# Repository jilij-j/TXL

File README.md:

TXL is a project to build classical distortion FX as eurorack modules with CV.

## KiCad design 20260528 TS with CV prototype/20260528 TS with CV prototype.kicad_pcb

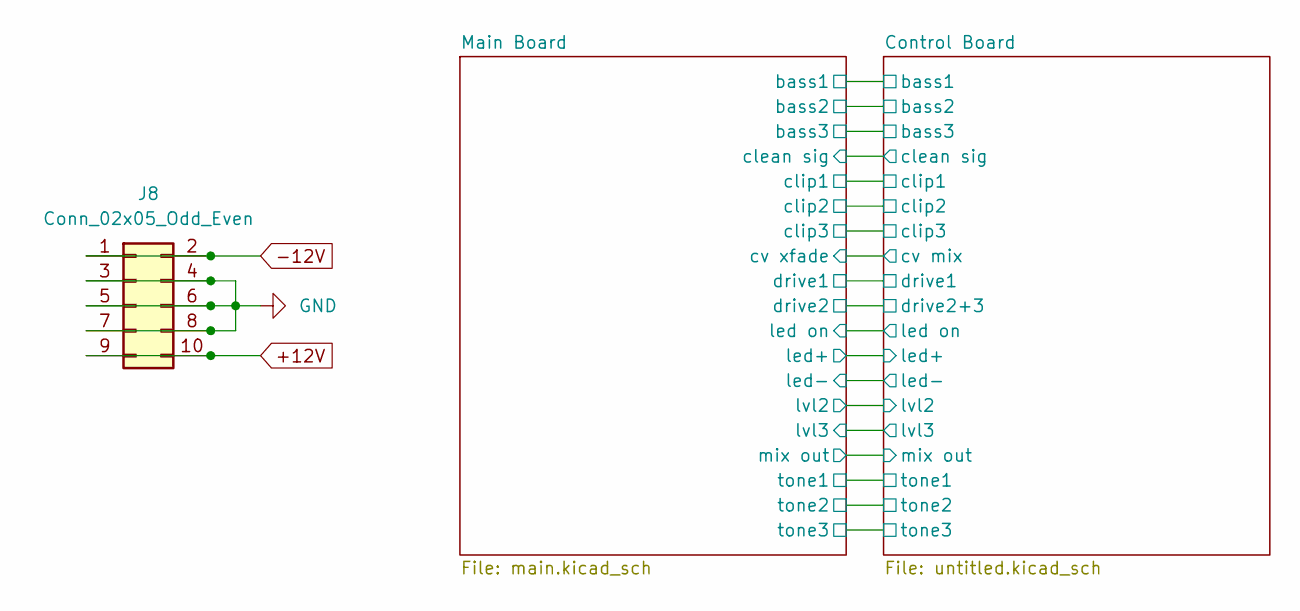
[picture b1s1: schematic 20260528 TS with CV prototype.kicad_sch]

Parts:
J8: Conn_02x05_Odd_Even; IDC-Header_2x05_P2.54mm_Vertical

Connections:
+12V: J8.9, J8.10; also elsewhere on the board
-12V: J8.1, J8.2; also elsewhere on the board
GND: J8.3, J8.4, J8.5, J8.6, J8.7, J8.8; also elsewhere on the board

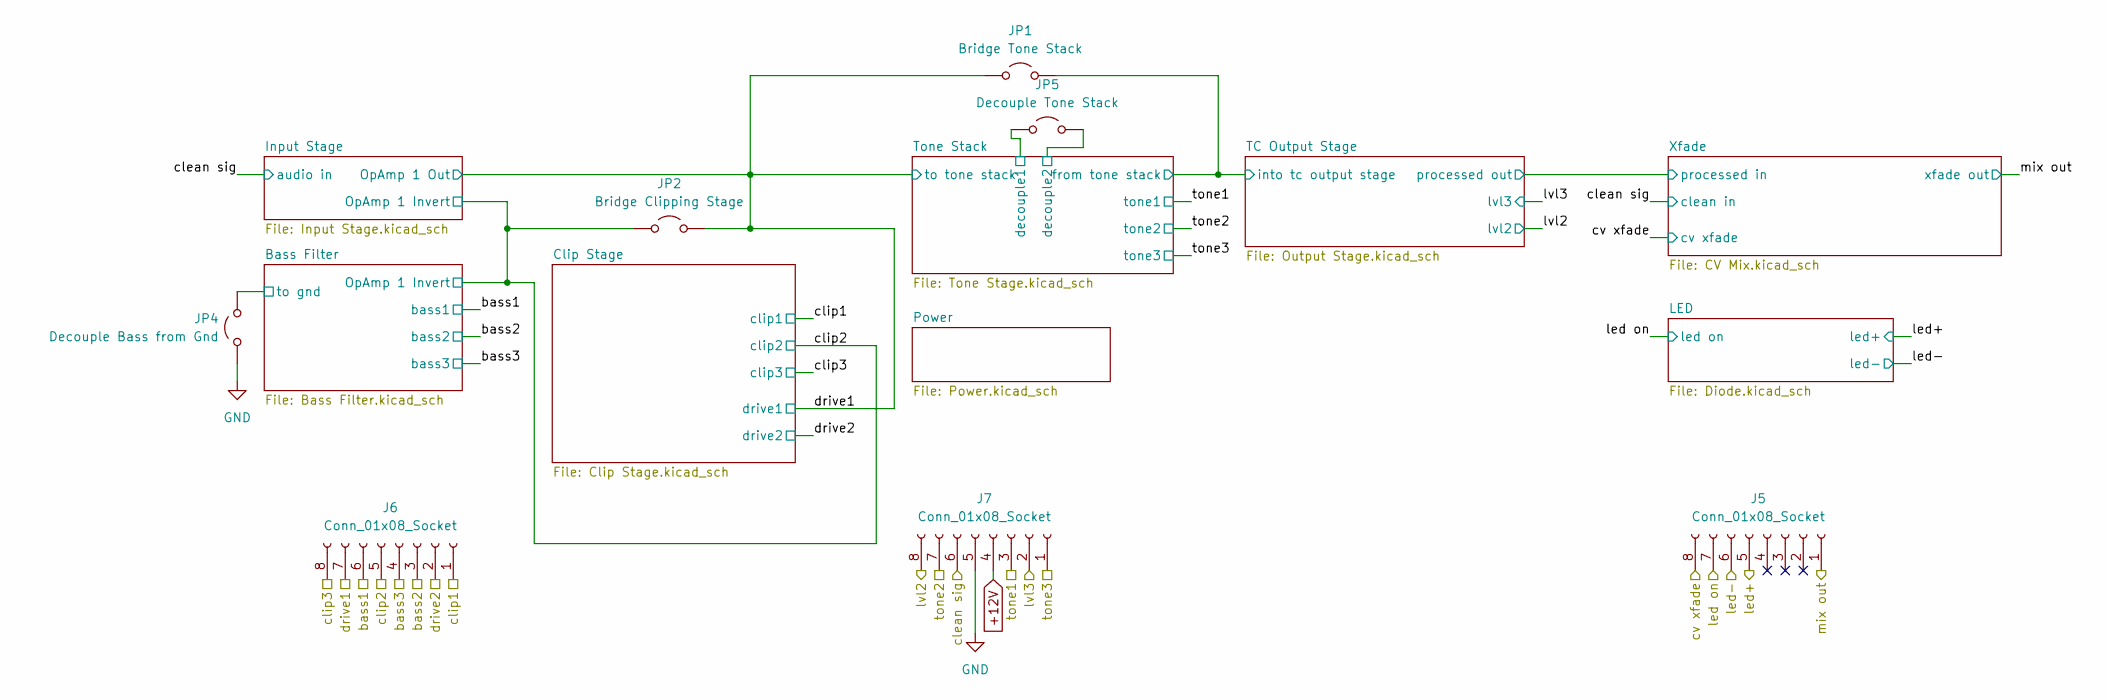
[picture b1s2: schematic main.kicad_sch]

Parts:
J5, J6, J7: Conn_01x08_Socket; PinSocket_1x08_P2.54mm_Vertical
JP1: Bridge Tone Stack; PinHeader_1x02_P2.54mm_Vertical
JP2: Bridge Clipping Stage; PinHeader_1x02_P2.54mm_Vertical
JP4: Decouple Bass from Gnd; PinHeader_1x02_P2.54mm_Vertical
JP5: Decouple Tone Stack; PinHeader_1x02_P2.54mm_Vertical

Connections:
+12V: J7.4; also elsewhere on the board
/Control Board/bass1: J6.6; also elsewhere on the board
/Control Board/bass2: J6.3; also elsewhere on the board
/Control Board/bass3: J6.4; also elsewhere on the board
/Control Board/clean sig: J7.6; also elsewhere on the board
/Control Board/clip1: J6.1; also elsewhere on the board
/Control Board/clip2: J6.5, JP2.1 (A); also elsewhere on the board
/Control Board/clip3: J6.8; also elsewhere on the board
/Control Board/cv mix: J5.8; also elsewhere on the board
/Control Board/drive1: J6.7, JP1.1 (A), JP2.2 (B); also elsewhere on the board
/Control Board/drive2+3: J6.2; also elsewhere on the board
/Control Board/led on: J5.7; also elsewhere on the board
/Control Board/led+: J5.5; also elsewhere on the board
/Control Board/led-: J5.6; also elsewhere on the board
/Control Board/lvl2: J7.8; also elsewhere on the board
/Control Board/lvl3: J7.2; also elsewhere on the board
/Control Board/mix out: J5.1; also elsewhere on the board
/Control Board/tone1: J7.3, JP5.2 (B); also elsewhere on the board
/Control Board/tone2: J7.7; also elsewhere on the board
/Control Board/tone3: J7.1; also elsewhere on the board
/Main Board/Bass Filter/to gnd: JP4.1 (A); also elsewhere on the board
/Main Board/TC Output Stage/into tc output stage: JP1.2 (B); also elsewhere on the board
/Main Board/Tone Stack/decouple1: JP5.1 (A); also elsewhere on the board
GND: J7.5, JP4.2 (B); also elsewhere on the board

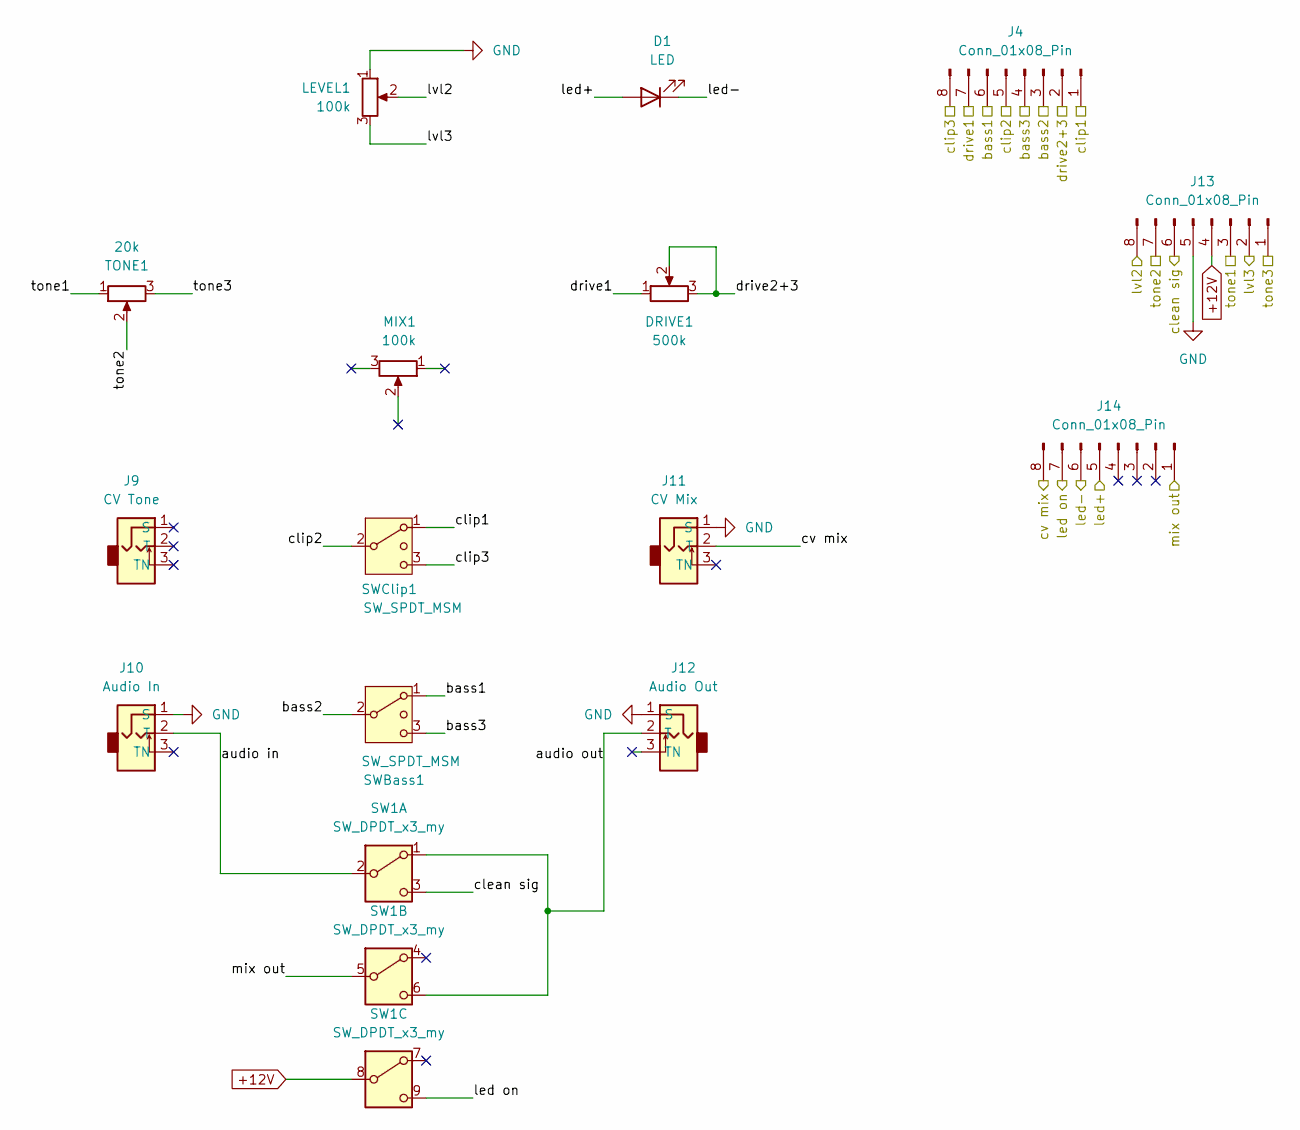
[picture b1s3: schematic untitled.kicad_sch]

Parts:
D1: LED; LED_D3.0mm
DRIVE1: 500k; Potentiometer_Alpha_RD901F-40-00D_Single_Vertical
J4, J13, J14: Conn_01x08_Pin; PinHeader_1x08_P2.54mm_Vertical
J9: CV Tone; EighthInch_PJ398SM
J10: Audio In; EighthInch_PJ398SM
J11: CV Mix; EighthInch_PJ398SM
J12: Audio Out; EighthInch_PJ398SM
LEVEL1: 100k; Potentiometer_Alpha_RD901F-40-00D_Single_Vertical
MIX1: 100k; Potentiometer_Alpha_RD901F-40-00D_Single_Vertical
SW1: SW_DPDT_x3_my; Switch_3PDT
SWBass1: SW_SPDT_MSM; M9040P
SWClip1: SW_SPDT_MSM; M9040P
TONE1: 20k; Potentiometer_Alpha_RD901F-40-00D_Single_Vertical

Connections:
+12V: J13.4, SW1.8 (B); also elsewhere on the board
/Control Board/audio in: J10.2 (T), SW1.2 (B)
/Control Board/audio out: J12.2 (T), SW1.1 (A), SW1.6 (C)
/Control Board/bass1: J4.6, SWBass1.1; also elsewhere on the board
/Control Board/bass2: J4.3, SWBass1.2 (3); also elsewhere on the board
/Control Board/bass3: J4.4, SWBass1.3 (4); also elsewhere on the board
/Control Board/clean sig: J13.6, SW1.3 (C); also elsewhere on the board
/Control Board/clip1: J4.1, SWClip1.1; also elsewhere on the board
/Control Board/clip2: J4.5, SWClip1.2 (3); also elsewhere on the board
/Control Board/clip3: J4.8, SWClip1.3 (4); also elsewhere on the board
/Control Board/cv mix: J11.2 (T), J14.8; also elsewhere on the board
/Control Board/drive1: DRIVE1.1, J4.7; also elsewhere on the board
/Control Board/drive2+3: DRIVE1.2, DRIVE1.3, J4.2; also elsewhere on the board
/Control Board/led on: J14.7, SW1.9 (C); also elsewhere on the board
/Control Board/led+: D1.2 (A), J14.5; also elsewhere on the board
/Control Board/led-: D1.1 (K), J14.6; also elsewhere on the board
/Control Board/lvl2: J13.8, LEVEL1.2; also elsewhere on the board
/Control Board/lvl3: J13.2, LEVEL1.3; also elsewhere on the board
/Control Board/mix out: J14.1, SW1.5 (B); also elsewhere on the board
/Control Board/tone1: J13.3, TONE1.1; also elsewhere on the board
/Control Board/tone2: J13.7, TONE1.2; also elsewhere on the board
/Control Board/tone3: J13.1, TONE1.3; also elsewhere on the board
GND: J10.1 (S), J11.1 (S), J12.1 (S), J13.5, LEVEL1.1; also elsewhere on the board

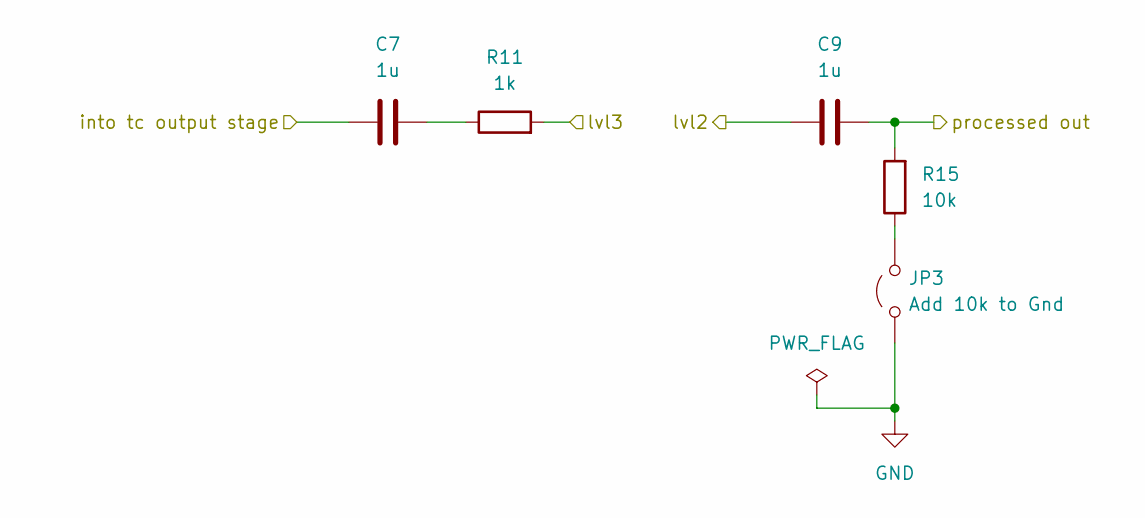
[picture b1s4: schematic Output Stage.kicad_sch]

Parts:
C7, C9: 1u; C_Disc_D4.3mm_W1.9mm_P5.00mm
JP3: Add 10k to Gnd; PinHeader_1x02_P2.54mm_Vertical
R11: 1k; R_Axial_DIN0204_L3.6mm_D1.6mm_P5.08mm_Horizontal
R15: 10k; R_Axial_DIN0204_L3.6mm_D1.6mm_P10.16mm_Horizontal

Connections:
/Control Board/lvl2: C9.1; also elsewhere on the board
/Control Board/lvl3: R11.2; also elsewhere on the board
/Main Board/TC Output Stage/into tc output stage: C7.1; also elsewhere on the board
/Main Board/TC Output Stage/processed out: C9.2, R15.2; also elsewhere on the board
GND: JP3.1 (A); also elsewhere on the board
unnamed: C7.2, R11.1
unnamed: JP3.2 (B), R15.1

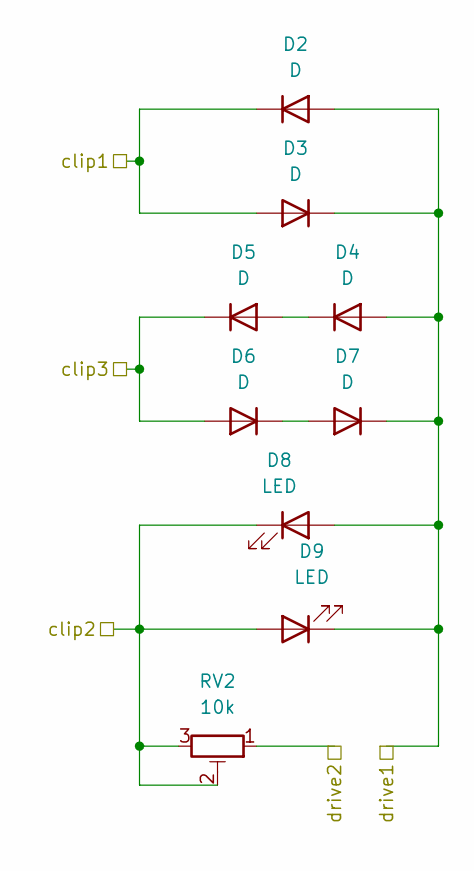
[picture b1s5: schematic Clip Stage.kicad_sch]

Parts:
D2, D3, D4, D5, D6, D7: D; D_T-1_P5.08mm_Horizontal
D8, D9: LED; LED_D3.0mm
RV2: 10k; Potentiometer_Runtron_RM-065_Vertical

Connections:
/Control Board/clip1: D2.1 (K), D3.2 (A); also elsewhere on the board
/Control Board/clip2: D8.1 (K), D9.2 (A), RV2.2, RV2.3; also elsewhere on the board
/Control Board/clip3: D5.1 (K), D6.2 (A); also elsewhere on the board
/Control Board/drive1: D2.2 (A), D3.1 (K), D4.2 (A), D7.1 (K), D8.2 (A), D9.1 (K); also elsewhere on the board
/Control Board/drive2+3: RV2.1; also elsewhere on the board
unnamed: D4.1 (K), D5.2 (A)
unnamed: D6.1 (K), D7.2 (A)

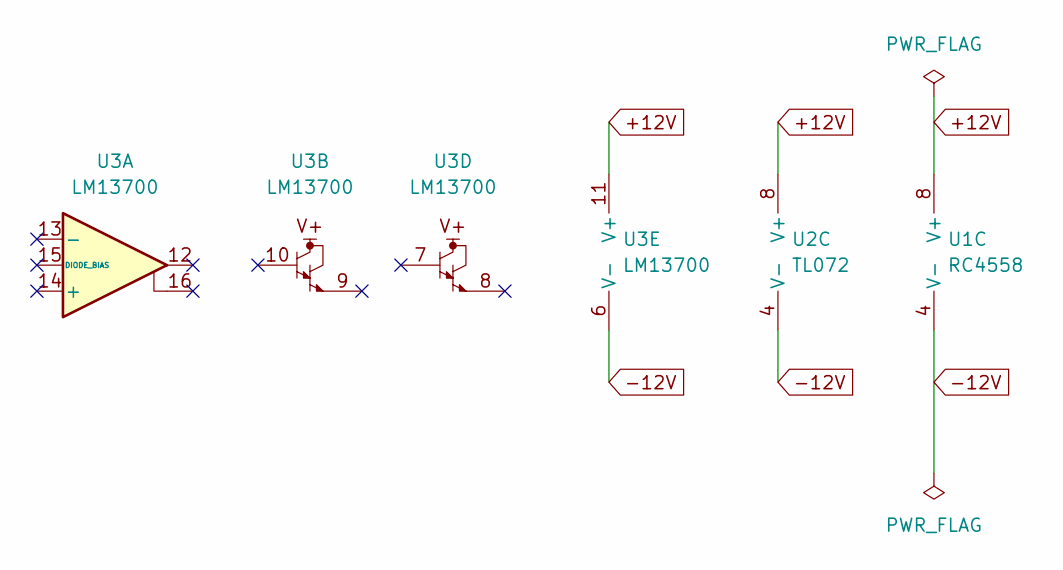
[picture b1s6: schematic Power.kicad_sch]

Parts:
U1: RC4558; DIP-8_W7.62mm
U2: TL072; DIP-8_W7.62mm_Socket
U3: LM13700; DIP-16_W7.62mm_Socket

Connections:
+12V: U1.8 (V+), U2.8 (V+), U3.11 (V+); also elsewhere on the board
-12V: U1.4 (V-), U2.4 (V-), U3.6 (V-); also elsewhere on the board

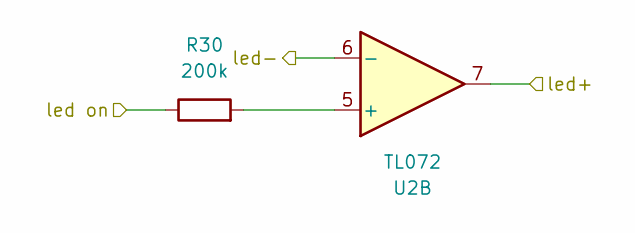
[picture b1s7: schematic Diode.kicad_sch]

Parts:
R30: 200k; R_Axial_DIN0204_L3.6mm_D1.6mm_P10.16mm_Horizontal
U2: TL072; DIP-8_W7.62mm_Socket

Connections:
/Control Board/led on: R30.1; also elsewhere on the board
/Control Board/led+: U2.7; also elsewhere on the board
/Control Board/led-: U2.6 (-); also elsewhere on the board
unnamed: R30.2, U2.5 (+)

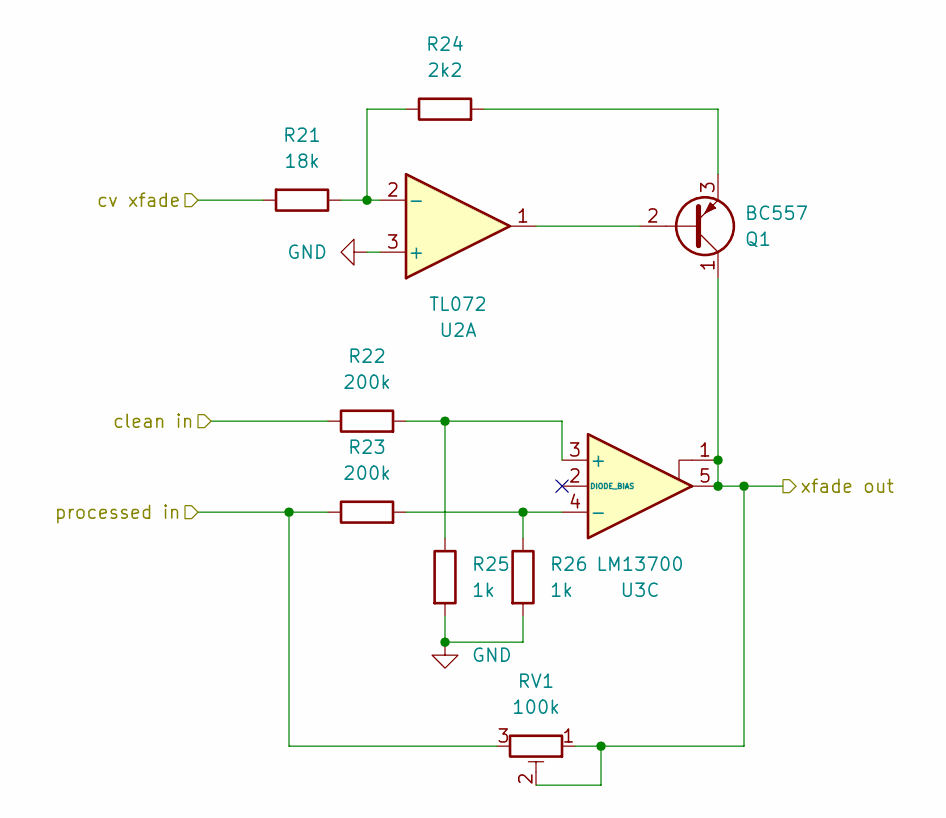
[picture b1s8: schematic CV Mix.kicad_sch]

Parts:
Q1: BC557; TO-92_Inline
R21: 18k; R_Axial_DIN0204_L3.6mm_D1.6mm_P7.62mm_Horizontal
R22, R23: 200k; R_Axial_DIN0204_L3.6mm_D1.6mm_P5.08mm_Horizontal
R24: 2k2; R_Axial_DIN0204_L3.6mm_D1.6mm_P7.62mm_Horizontal
R25: 1k; R_Axial_DIN0204_L3.6mm_D1.6mm_P7.62mm_Horizontal
R26: 1k; R_Axial_DIN0204_L3.6mm_D1.6mm_P10.16mm_Horizontal
RV1: 100k; Potentiometer_Runtron_RM-065_Vertical
U2: TL072; DIP-8_W7.62mm_Socket
U3: LM13700; DIP-16_W7.62mm_Socket

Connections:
/Control Board/clean sig: R22.1; also elsewhere on the board
/Control Board/cv mix: R21.2; also elsewhere on the board
/Control Board/mix out: Q1.1 (C), RV1.1, RV1.2, U3.1, U3.5; also elsewhere on the board
/Main Board/TC Output Stage/processed out: R23.1, RV1.3; also elsewhere on the board
GND: R25.2, R26.2, U2.3 (+); also elsewhere on the board
unnamed: Q1.2 (B), U2.1
unnamed: Q1.3 (E), R24.2
unnamed: R21.1, R24.1, U2.2 (-)
unnamed: R22.2, R25.1, U3.3 (+)
unnamed: R23.2, R26.1, U3.4 (-)

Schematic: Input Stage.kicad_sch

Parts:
C2: 1u; C_Disc_D4.3mm_W1.9mm_P5.00mm
C3: 47p; C_Disc_D3.0mm_W1.6mm_P2.50mm
R4: 10k; R_Axial_DIN0204_L3.6mm_D1.6mm_P10.16mm_Horizontal
U1: RC4558; DIP-8_W7.62mm

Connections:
/Control Board/clean sig: C2.1; also elsewhere on the board
/Control Board/clip2: C3.1, U1.2 (-); also elsewhere on the board
/Control Board/drive1: C3.2, U1.1; also elsewhere on the board
GND: R4.1; also elsewhere on the board
unnamed: C2.2, R4.2, U1.3 (+)

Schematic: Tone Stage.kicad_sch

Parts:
C5, C6: 220n; C_Disc_D4.3mm_W1.9mm_P5.00mm
R7: 1k; R_Axial_DIN0204_L3.6mm_D1.6mm_P10.16mm_Horizontal
R8: 10k; R_Axial_DIN0204_L3.6mm_D1.6mm_P5.08mm_Horizontal
R9: 220; R_Axial_DIN0204_L3.6mm_D1.6mm_P5.08mm_Horizontal
R10: 1k; R_Axial_DIN0204_L3.6mm_D1.6mm_P2.54mm_Vertical
U1: RC4558; DIP-8_W7.62mm

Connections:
/Control Board/drive1: R7.1; also elsewhere on the board
/Control Board/tone1: C5.1, R8.1, U1.5 (+); also elsewhere on the board
/Control Board/tone2: C6.1; also elsewhere on the board
/Control Board/tone3: R10.1, U1.6 (-); also elsewhere on the board
/Main Board/TC Output Stage/into tc output stage: R10.2, U1.7; also elsewhere on the board
/Main Board/Tone Stack/decouple1: R7.2; also elsewhere on the board
GND: C5.2, R8.2, R9.2; also elsewhere on the board
unnamed: C6.2, R9.1

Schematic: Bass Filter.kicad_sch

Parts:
C1: 47n; C_Disc_D4.3mm_W1.9mm_P5.00mm
CX2: 22n; C_Disc_D4.3mm_W1.9mm_P5.00mm
CX3: 68n; C_Disc_D4.3mm_W1.9mm_P5.00mm
R5: 4.7k; R_Axial_DIN0207_L6.3mm_D2.5mm_P12.70mm_Horizontal_my

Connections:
/Control Board/bass1: CX2.1; also elsewhere on the board
/Control Board/bass2: C1.1, R5.2; also elsewhere on the board
/Control Board/bass3: CX3.1; also elsewhere on the board
/Control Board/clip2: C1.2, CX2.2, CX3.2; also elsewhere on the board
/Main Board/Bass Filter/to gnd: R5.1; also elsewhere on the board

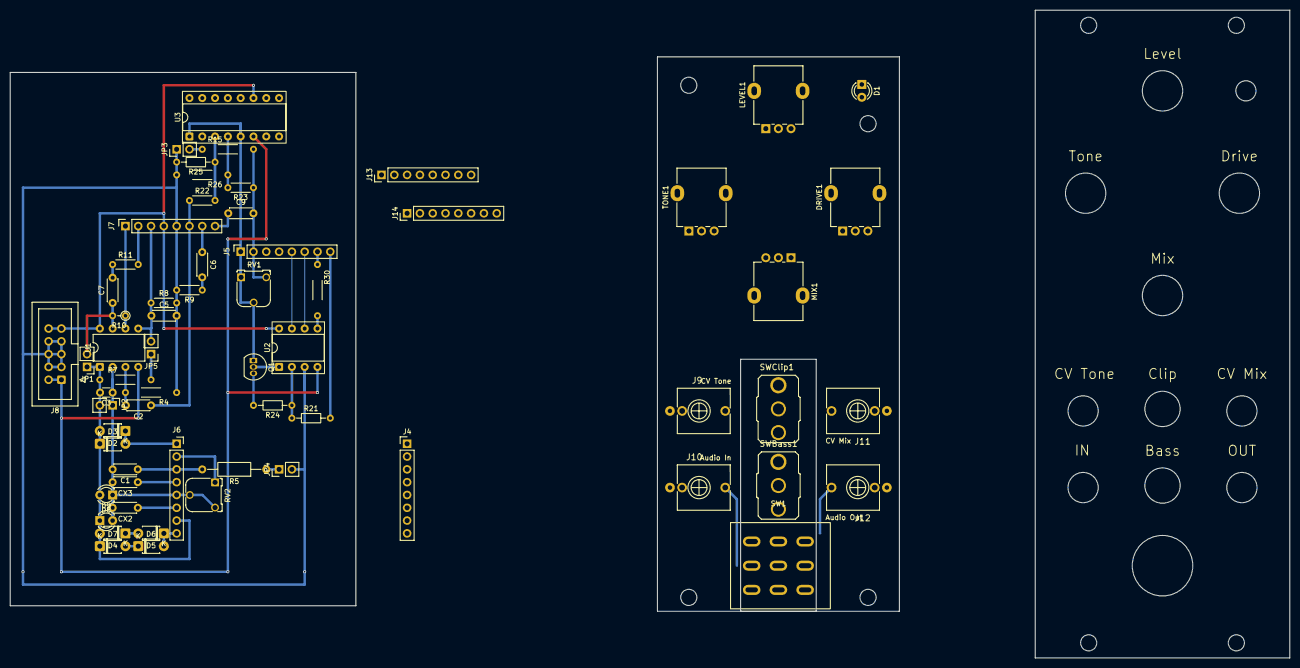
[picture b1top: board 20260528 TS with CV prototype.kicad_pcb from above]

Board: 2 copper layers, 253.8 x 128.4 mm, 62 parts (0 on the bottom side), 40 nets.

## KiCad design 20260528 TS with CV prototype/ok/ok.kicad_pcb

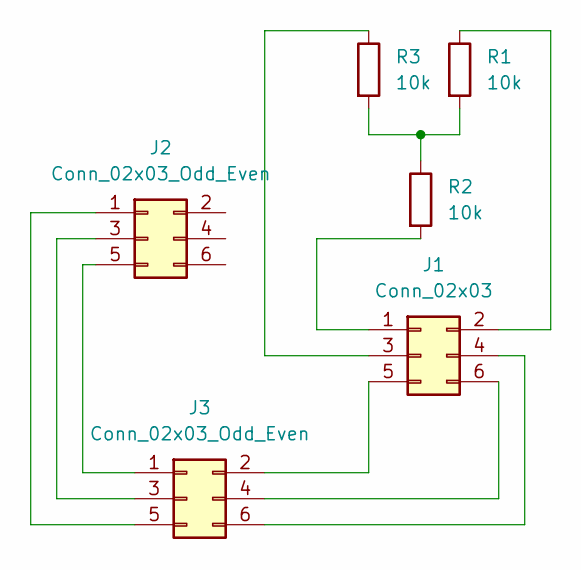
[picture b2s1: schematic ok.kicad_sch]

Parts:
J1: Conn_02x03; PinHeader_2x03_P2.54mm_Vertical; Part Number LL1009-2A, 2.54MM 2*3PIN HEADER,LENGTH=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
J2, J3: Conn_02x03_Odd_Even; PinSocket_2x03_P2.54mm_Horizontal
R1, R2, R3: 10k; R_Axial_DIN0204_L3.6mm_D1.6mm_P1.90mm_Vertical

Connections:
unnamed: J1.1 (+12V), R2.2
unnamed: J1.2 (+12V), R1.1
unnamed: J1.3 (GND), R3.1
unnamed: J2.1, J3.5
unnamed: J2.3, J3.3
unnamed: J2.5, J3.1
unnamed: J1.5 (GND), J3.2
unnamed: J1.6 (GND), J3.4
unnamed: J1.4 (GND), J3.6
unnamed: R1.2, R2.1, R3.2

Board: 2 copper layers, 6 parts (0 on the bottom side), 10 nets, no tracks yet.

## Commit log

2026-05-29 änderung
2026-05-29 gitignore für KiCad
2026-05-29 new gitignore
2026-05-29 git ignore should ignor compressed files
2026-05-29 geht das??
2026-05-29 4558
2026-05-29 ignore zip files
2026-05-29 clean up
2026-05-29 everything but zip
